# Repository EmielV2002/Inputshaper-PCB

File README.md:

# Input shaper PCB

## Backstory

Hi, thank you for taking interest in my design!
In the summer of 2021 I saw the crampon PCB made by annex engineering. It looked like a pretty simple design and I have always been interested in PCB design so I thought this would be a fun beginner project. The result of my adventure can be found on this GitHub page. However, Annex's design probably looks, feels and works better. I have not been able tot test my design yet as well. So proceed with caution!

The link to Annex's product can be found here: [Annex engineering home page](https://annex-engineering.eu/)
Link to their Crampon GitHub page: [Crampon GitHub page](https://github.com/Annex-Engineering/Annex_Engineering_PCBs/tree/master/crampon)

## Technical details

This PCB is based on the RP2040 chip. the PCB uses an ADXL345 accelerometer to measure the harmonic frequencies of your 3d-printer during a input shape tuning test.
More information about input shaping can be found here: [Klipper3d.org](https://www.klipper3d.org/Resonance_Compensation.html)
I have also added a BME280 temperature, barometric pressure and humidity sensor, but this is not mandatory.

This is one of my very fist PCB designs and I made it by implementing schematics I found on the internet.
My sources are listed here:

overall design: [RP2040 Hardware design](https://datasheets.raspberrypi.com/rp2040/hardware-design-with-rp2040.pdf)
BME280 design:  [BME280 datasheet](https://www.bosch-sensortec.com/media/boschsensortec/downloads/datasheets/bst-bme280-ds002.pdf)
ADXL345 design: [ADXK345 datasheet](https://cdn.sparkfun.com/datasheets/Sensors/Accelerometers/ADXL345_Breakout.pdf)

## Manual

to be added.

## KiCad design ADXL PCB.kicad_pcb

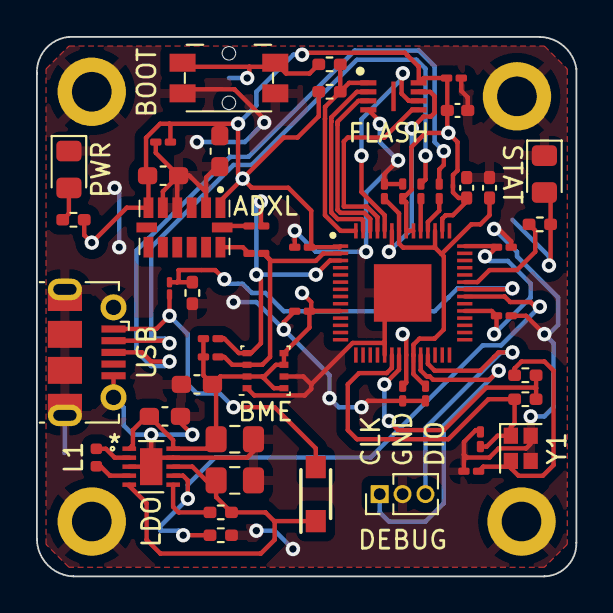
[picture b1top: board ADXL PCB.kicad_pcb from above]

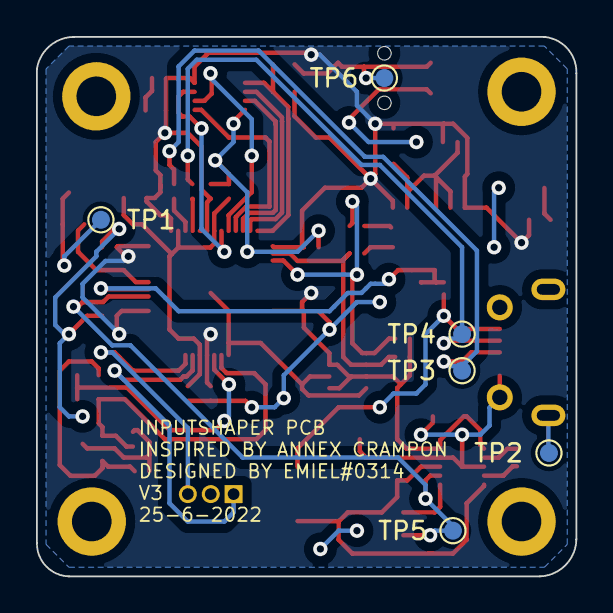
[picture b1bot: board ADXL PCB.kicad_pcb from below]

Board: 2 copper layers, 30.0 x 30.0 mm, 60 parts (6 on the bottom side), 33 nets.

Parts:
AC1: ADXL345BCCZ-RL7; CC-14-1
C1, C2: 15p; C_0201_0603Metric_Pad0.64x0.40mm_HandSolder
C3, C6: 2u2; C_0201_0603Metric_Pad0.64x0.40mm_HandSolder
C4, C5, C7, C8, C11, C12, C16: 100n; C_0201_0603Metric_Pad0.64x0.40mm_HandSolder
C9, C10, C15: 2u2; C_0402_1005Metric_Pad0.74x0.62mm_HandSolder
C13, C14: 47u; C_0805_2012Metric_Pad1.18x1.45mm_HandSolder
C17, C20, C21: 0.1uf; C_0603_1608Metric_Pad1.08x0.95mm_HandSolder
C18: 10uf; C_0603_1608Metric_Pad1.08x0.95mm_HandSolder
C19: 10uf1; C_0201_0603Metric_Pad0.64x0.40mm_HandSolder
D1, D2: LED; LED_0805_2012Metric_Pad1.15x1.40mm_HandSolder
D3: MBR120VLSFT1G; SODFL3616X98N
H1, H2, H3, H4: MountingHole_Pad; MountingHole_2.2mm_M2_DIN965_Pad
IC1: RP2040; QFN40P700X700X90-57N-D
IC2: W25Q16JVUXIQ; SON50P300X200X60-9N
J1: Conn_01x03_Male; PinHeader_1x03_P1.27mm_Vertical
J2: USB_B_Micro; USB_Micro-B_Molex-105017-0001
L1: 2u2; L_0402_1005Metric
R1: 4.7k; R_0402_1005Metric_Pad0.72x0.64mm_HandSolder
R2, R12: DNP; R_0402_1005Metric_Pad0.72x0.64mm_HandSolder
R3, R11: 1k; R_0402_1005Metric_Pad0.72x0.64mm_HandSolder
R4, R8: 10k; R_0402_1005Metric_Pad0.72x0.64mm_HandSolder
R5, R6: 27r; R_0201_0603Metric_Pad0.64x0.40mm_HandSolder
R7: 5k6; R_01005_0402Metric_Pad0.57x0.30mm_HandSolder
R9, R10: 100k; R_0402_1005Metric_Pad0.72x0.64mm_HandSolder
R13, R14, R15, R16: 4.7k; R_0201_0603Metric_Pad0.64x0.40mm_HandSolder
SW1: SW_Push; Panasonic_EVQPUM_EVQPUD
TP1, TP2, TP3, TP4, TP5, TP6: TestPoint; TestPoint_Pad_D1.0mm
U1: RT6150B-33GQW
U2: BME280; Bosch_LGA-8_2.5x2.5mm_P0.65mm_ClockwisePinNumbering
Y1: 12MHz; Crystal_SMD_2016-4Pin_2.0x1.6mm

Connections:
+1V1: C6.1, C8.1, C9.1, IC1.23 (DVDD_1), IC1.45 (VREG_VOUT), IC1.50 (DVDD_2)
+3V3: AC1.1 (VDD_I/O), AC1.6 (VS), C3.1, C4.1, C5.1, C7.1, C10.1, C11.1, C12.1, C14.1, C15.1, C16.1, C17.1, C18.2, C19.2, C20.1, C21.1, IC1.1 (IOVDD_1), IC1.10 (IOVDD_2), IC1.22 (IOVDD_3), IC1.33 (IOVDD_4), IC1.42 (IOVDD_5), IC1.44 (VREG_VIN), IC1.48 (USB_VDD), IC1.49 (IOVDD_6), IC2.8 (VCC), R4.2, R12.1, R13.2, R14.2, U1.1 (VOUT), U1.10 (FB), U2.2 (CSB), U2.5 (SDO), U2.6 (VDDIO), U2.8 (VDD)
/3V3_EN: R9.1, U1.6 (EN)
/GPIO23: IC1.35 (GPIO23), R10.1, TP5.1, U1.7 (PS)
/GPIO24: IC1.36 (GPIO24), R7.2, R8.1
/GPIO25: IC1.37 (GPIO25), R1.2
/QSPI_SCLK: IC1.52 (QSPI_SCLK), IC2.6 (CLK)
/QSPI_SD0: IC1.53 (QSPI_SD0), IC2.5 (DI_(IO0))
/QSPI_SD1: IC1.55 (QSPI_SD1), IC2.2 (DO_(IO1))
/QSPI_SD2: IC1.54 (QSPI_SD2), IC2.3 (~WP_(IO2))
/QSPI_SD3: IC1.51 (QSPI_SD3), IC2.7 (~HOLD_OR_RESET_(IO3))
/QSPI_SS: IC1.56 (QSPI_SS_N), IC2.1 (~CS), R11.2, R12.2
/SCL: IC1.3 (GPIO1), R14.1, R15.2, U2.4 (SCK)
/SDA: IC1.2 (GPIO0), R13.1, R16.2, U2.3 (SDI)
/SWCLK: IC1.24 (SWCLK), J1.1
/SWDIO: IC1.25 (SWDIO), J1.3
/USB_DM: J2.3 (D+), R6.1, TP3.1
/USB_DMX: IC1.46 (USB_DM), R6.2
/USB_DP: J2.2 (D-), R5.1, TP4.1
/USB_DPX: IC1.47 (USB_DP), R5.2
/XIN: C1.1, IC1.20 (XIN), R2.2, Y1.1
/XOUT: IC1.21 (XOUT), R2.1, R3.1
/XR: C2.1, R3.2, Y1.2
GNDREF: AC1.2 (GND_1), AC1.4 (GND_2), AC1.5 (GND_3), C1.2, C2.2, C3.2, C4.2, C5.2, C6.2, C7.2, C8.2, C9.2, C10.2, C11.2, C12.2, C13.2, C14.2, C15.2, C16.2, C17.2, C18.1, C19.1, C20.2, C21.2, D1.1 (K), D2.1 (K), H1.1, H2.1, H3.1, H4.1, IC1.19 (TESTEN), IC1.57 (GND), IC2.4 (GND), J1.2, J2.5 (GND), J2.6 (Shield), R8.2, R10.2, SW1.2, TP2.1, U1.3 (GND), U1.9 (GND), U1.11 (GND), U2.1 (GND), U2.7 (GND), Y1.3, Y1.4
unnamed: AC1.13 (SDA/SDI/SDIO), R16.1
unnamed: AC1.14 (SCL/SCLK), R15.1
unnamed: D1.2 (A), R1.1, TP1.1
unnamed: D2.2 (A), R4.1
unnamed: L1.1, U1.2 (LX2)
unnamed: L1.2, U1.4 (LX1)
unnamed: R11.1, SW1.1, TP6.1
VBUS: D3.2, J2.1 (VBUS), R7.1
VSS: C13.1, D3.1, R9.2, U1.5 (VIN), U1.8 (VINA)

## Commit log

2023-01-22 Added PCB design files
2023-02-12 add backup

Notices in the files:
parts and their libraries:
Copyright 2021 Accelerated Designs. All rights reserved.
